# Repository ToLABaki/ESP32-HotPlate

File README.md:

# ESP32-HotPlate
A reflow soldering plate, using the ESP32 and the lvgl graphics library.

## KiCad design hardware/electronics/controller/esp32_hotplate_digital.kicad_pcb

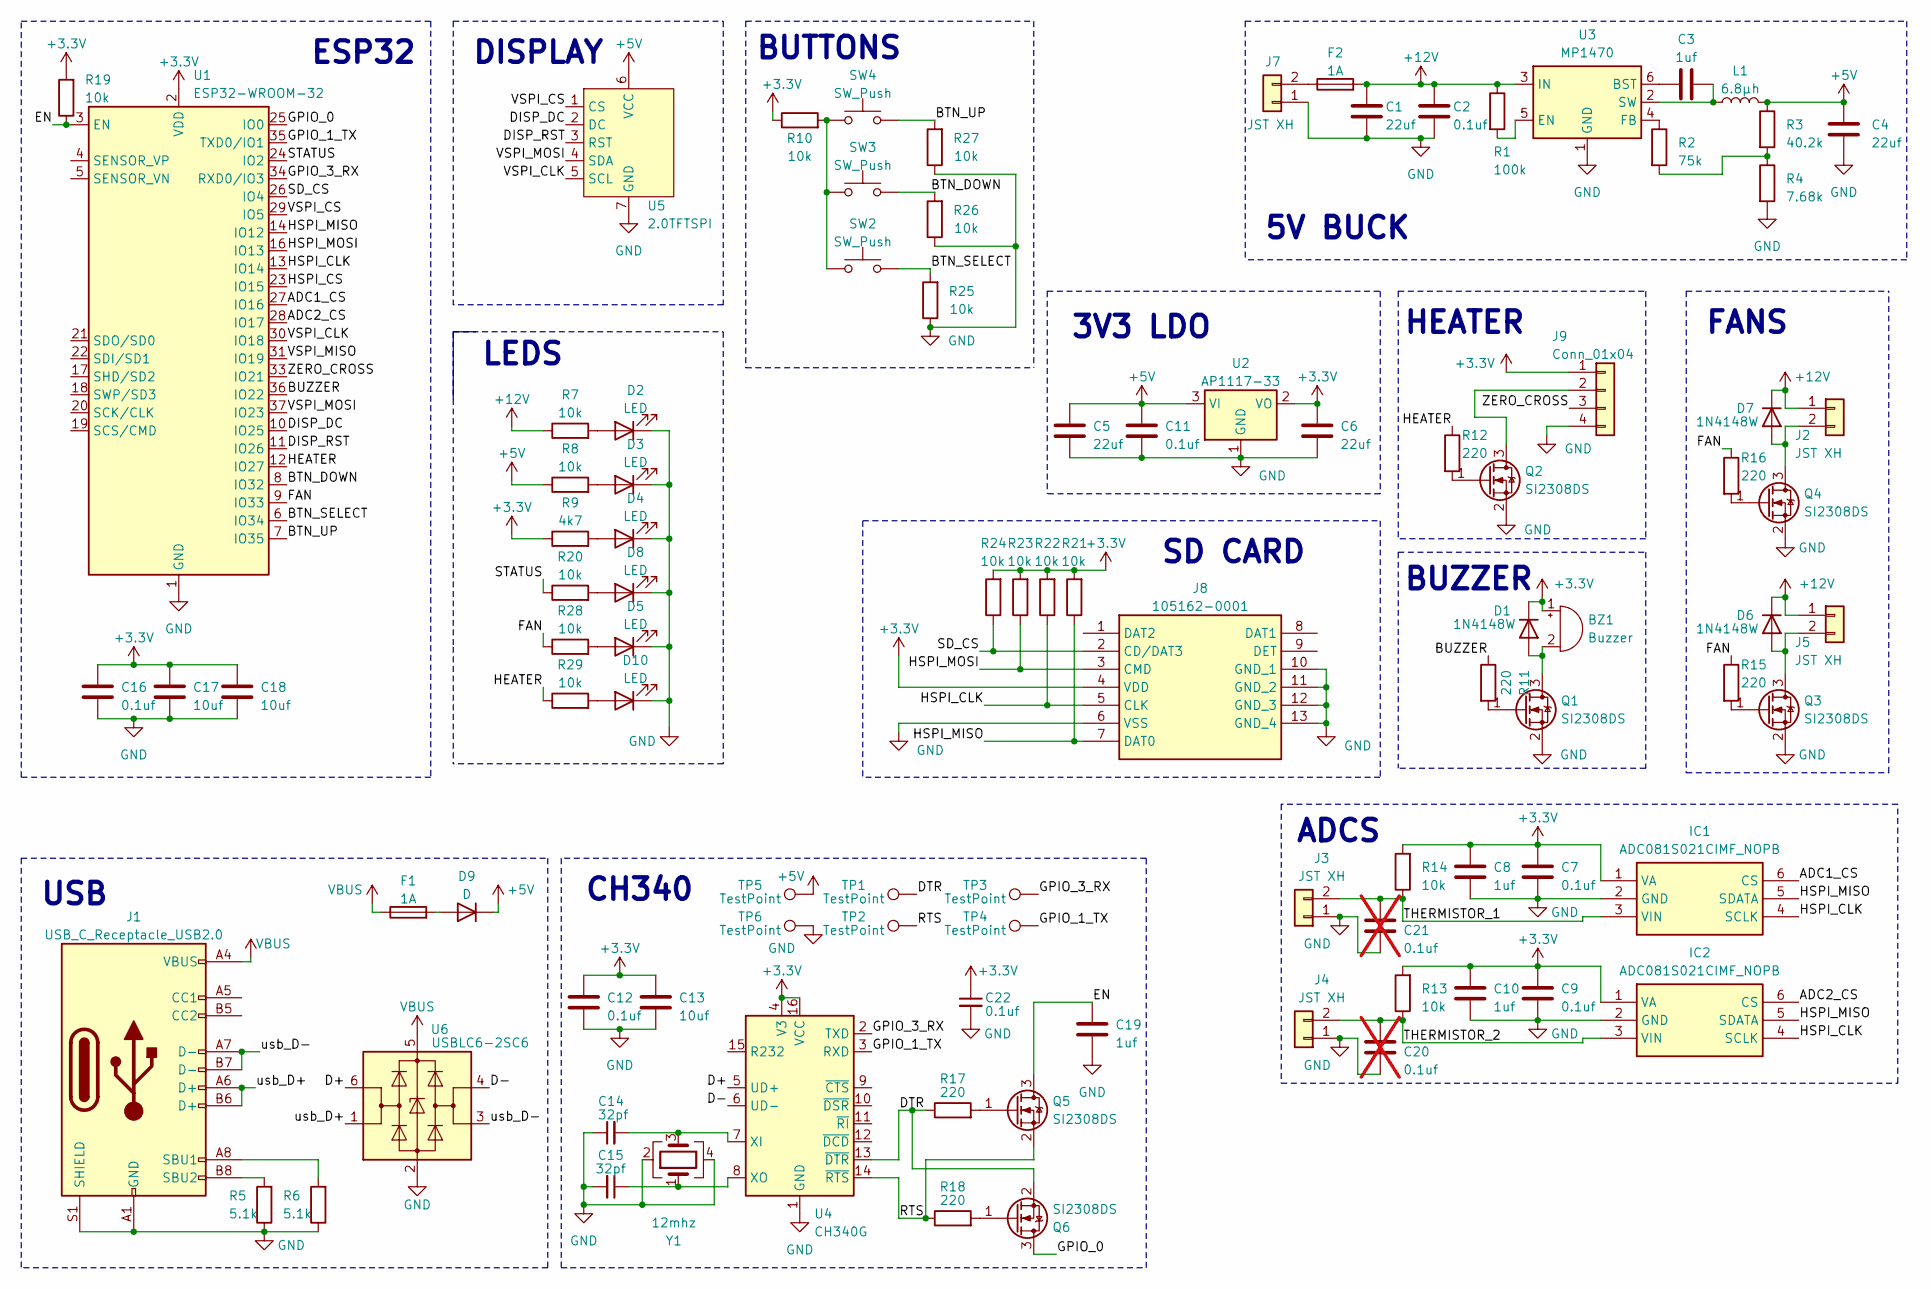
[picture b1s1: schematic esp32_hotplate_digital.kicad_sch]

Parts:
BZ1: Buzzer; PUIAudio_SMT_0825_S_4_R
C1, C4, C5, C6: 22uf; C_1206_3216Metric_Pad1.33x1.80mm_HandSolder
C2, C7, C9, C11, C12, C16: 0.1uf; C_0805_2012Metric_Pad1.18x1.45mm_HandSolder
C3, C8, C10, C19: 1uf; C_0805_2012Metric_Pad1.18x1.45mm_HandSolder
C13, C17, C18: 10uf; C_0805_2012Metric_Pad1.18x1.45mm_HandSolder
C14, C15: 32pf; C_0603_1608Metric_Pad1.08x0.95mm_HandSolder
C20, C21: 0.1uf; C_0805_2012Metric_Pad1.18x1.45mm_HandSolder; not fitted
C22: 0.1uf; C_0603_1608Metric_Pad1.08x0.95mm_HandSolder
D1, D6, D7: 1N4148W; D_SOD-128
D2, D3, D4, D5, D8, D10: LED; LED_0805_2012Metric_Pad1.15x1.40mm_HandSolder
D9: D; DIOM5226X240N
F1, F2: 1A; Fuse_1206_3216Metric
IC1, IC2: ADC081S021CIMF_NOPB; SOT95P280X145-6N; Mouser Part Number 926-AD081S021CIMFNPB
J1: USB_C_Receptacle_USB2.0; USB_C_Receptacle_HRO_TYPE-C-31-M-12
J2, J3, J4, J5, J7: JST XH; JST_XH_B2B-XH-A_1x02_P2.50mm_Vertical
J8: 105162-0001; TF-SMD_TF-PUSH; Mouser Part Number 538-105162-0001
J9: Conn_01x04; JST_XH_B4B-XH-A_1x04_P2.50mm_Vertical
L1: 6.8μh; L_Changjiang_FNR8040S
Q1, Q2, Q3, Q4, Q5, Q6: SI2308DS; SOT-23
R1: 100k; R_0805_2012Metric_Pad1.20x1.40mm_HandSolder
R2: 75k; R_0805_2012Metric_Pad1.20x1.40mm_HandSolder
R3: 40.2k; R_0805_2012Metric_Pad1.20x1.40mm_HandSolder
R4: 7.68k; R_0805_2012Metric_Pad1.20x1.40mm_HandSolder
R5, R6: 5.1k; R_0805_2012Metric_Pad1.20x1.40mm_HandSolder
R7, R8, R10, R13, R14, R19, R20, R21, R22, R23, R24, R25, R26, R27, R28, R29: 10k; R_0805_2012Metric_Pad1.20x1.40mm_HandSolder
R9: 4k7; R_0805_2012Metric_Pad1.20x1.40mm_HandSolder
R11, R12, R15, R16, R17, R18: 220; R_0805_2012Metric_Pad1.20x1.40mm_HandSolder
SW2, SW3, SW4: SW_Push; SW_SPST_TL3342
TP1, TP2, TP3, TP4, TP5, TP6: TestPoint; TestPoint_Pad_2.0x2.0mm
U1: ESP32-WROOM-32
U2: AP1117-33; SOT-223-3_TabPin2
U3: MP1470; TSOT-23-6
U4: CH340G; SOIC-16_3.9x9.9mm_P1.27mm
U5: 2.0TFTSPI; 2.0_TFT_SPI
U6: USBLC6-2SC6; SOT-23-6
Y1: 12mhz; Crystal_SMD_3225-4Pin_3.2x2.5mm

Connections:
+3.3V: BZ1.1 (-), C6.1, C7.1, C8.1, C9.1, C10.1, C12.1, C13.1, C16.1, C17.1, C18.1, C22.1, D1.1 (K), IC1.1 (VA), IC2.1 (VA), J8.4 (VDD), J9.1, R9.1, R10.1, R13.2, R14.2, R19.2, R21.2, R22.2, R23.2, R24.2, U1.2 (VDD), U2.2 (VO), U4.4 (V3), U4.16 (VCC)
+5V: C4.1, C5.1, C11.1, D9.1 (K), L1.2, R3.1, R8.1, TP5.1, U2.3 (VI), U5.6 (VCC)
+12V: C1.1, C2.1, D6.1 (K), D7.1 (K), F2.2, J2.1, J5.1, R1.1, R7.1, U3.3 (IN)
/ADC1_CS: IC1.6 (CS), U1.27 (IO16)
/ADC2_CS: IC2.6 (CS), U1.28 (IO17)
/BTN_DOWN: R26.2, SW3.2, U1.8 (IO32)
/BTN_SELECT: R25.2, SW2.2, U1.6 (IO34)
/BTN_UP: R27.2, SW4.2, U1.7 (IO35)
/BUZZER: R11.1, U1.36 (IO22)
/D+: U4.5 (UD+), U6.6 (I/O1)
/D-: U4.6 (UD-), U6.4 (I/O2)
/DISP_DC: U1.10 (IO25), U5.2 (DC)
/DISP_RST: U1.11 (IO26), U5.3 (RST)
/DTR: Q6.2 (S), R17.1, TP1.1, U4.13 (~DTR)
/EN: C19.2, Q5.3 (D), R19.1, U1.3 (EN)
/FAN: R15.1, R16.1, R28.1, U1.9 (IO33)
/GPIO_0: Q6.3 (D), U1.25 (IO0)
/GPIO_1_TX: TP4.1, U1.35 (TXD0/IO1), U4.3 (RXD)
/GPIO_3_RX: TP3.1, U1.34 (RXD0/IO3), U4.2 (TXD)
/HEATER: R12.1, R29.1, U1.12 (IO27)
/HSPI_CLK: IC1.4 (SCLK), IC2.4 (SCLK), J8.5 (CLK), R22.1, U1.13 (IO14)
/HSPI_CS: U1.23 (IO15)
/HSPI_MISO: IC1.5 (SDATA), IC2.5 (SDATA), J8.7 (DAT0), R21.1, U1.14 (IO12)
/HSPI_MOSI: J8.3 (CMD), R23.1, U1.16 (IO13)
/RTS: Q5.2 (S), R18.1, TP2.1, U4.14 (~RTS)
/SD_CS: J8.2 (CD/DAT3), R24.1, U1.26 (IO4)
/STATUS: R20.1, U1.24 (IO2)
/THERMISTOR_1: C21.1, IC1.3 (VIN), J3.2, R14.1
/THERMISTOR_2: C20.1, IC2.3 (VIN), J4.2, R13.1
/VSPI_CLK: U1.30 (IO18), U5.5 (SCL)
/VSPI_CS: U1.29 (IO5), U5.1 (CS)
/VSPI_MISO: U1.31 (IO19)
/VSPI_MOSI: U1.37 (IO23), U5.4 (SDA)
/ZERO_CROSS: J9.3, U1.33 (IO21)
/usb_D+: J1.A6 (D+), J1.B6 (D+), U6.1 (I/O1)
/usb_D-: J1.A7 (D-), J1.B7 (D-), U6.3 (I/O2)
GND: C1.2, C2.2, C4.2, C5.2, C6.2, C7.2, C8.2, C9.2, C10.2, C11.2, C12.2, C13.2, C14.1, C15.2, C16.2, C17.2, C18.2, C19.1, C20.2, C21.2, C22.2, D2.1 (K), D3.1 (K), D4.1 (K), D5.1 (K), D8.1 (K), D10.1 (K), IC1.2 (GND), IC2.2 (GND), J1.A1 (GND), J1.A12 (GND), J1.B1 (GND), J1.B12 (GND), J1.S1 (SHIELD), J3.1, J4.1, J7.1, J8.6 (VSS), J8.10 (GND_1), J8.11 (GND_2), J8.12 (GND_3), J8.13 (GND_4), J9.4, Q1.2 (S), Q2.2 (S), Q3.2 (S), Q4.2 (S), R4.2, R5.1, R6.1, R25.1, R26.1, R27.1, TP6.1, U1.1 (GND), U1.15 (GND), U1.38 (GND), U1.39 (GND), U2.1 (GND), U3.1 (GND), U4.1 (GND), U5.7 (GND), U6.2 (GND), Y1.2, Y1.4
unnamed: BZ1.2 (+), D1.2 (A), Q1.3 (D)
unnamed: D2.2 (A), R7.2
unnamed: D3.2 (A), R8.2
unnamed: D4.2 (A), R9.2
unnamed: D5.2 (A), R28.2
unnamed: D6.2 (A), J5.2, Q3.3 (D)
unnamed: D7.2 (A), J2.2, Q4.3 (D)
unnamed: D8.2 (A), R20.2
unnamed: D9.2 (A), F1.2
unnamed: D10.2 (A), R29.2
unnamed: J1.A8 (SBU1), R6.2
unnamed: J1.B8 (SBU2), R5.2
unnamed: F2.1, J7.2
unnamed: J9.2, Q2.3 (D)
unnamed: Q1.1 (G), R11.2
unnamed: Q2.1 (G), R12.2
unnamed: Q3.1 (G), R15.2
unnamed: Q4.1 (G), R16.2
unnamed: Q5.1 (G), R17.2
unnamed: Q6.1 (G), R18.2
unnamed: R2.2, R3.2, R4.1
unnamed: R10.2, SW2.1, SW3.1, SW4.1
unnamed: C3.1, U3.6 (BST)
unnamed: R1.2, U3.5 (EN)
unnamed: R2.1, U3.4 (FB)
unnamed: C3.2, L1.1, U3.2 (SW)
unnamed: C14.2, U4.7 (XI), Y1.3
unnamed: C15.1, U4.8 (XO), Y1.1
VBUS: F1.1, J1.A4 (VBUS), J1.A9 (VBUS), J1.B4 (VBUS), J1.B9 (VBUS), U6.5 (VBUS)

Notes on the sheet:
ESP32
HEATER
5V BUCK
FANS
BUTTONS
BUZZER
CH340
SD CARD
DISPLAY
ADCS
LEDS
3V3 LDO
USB

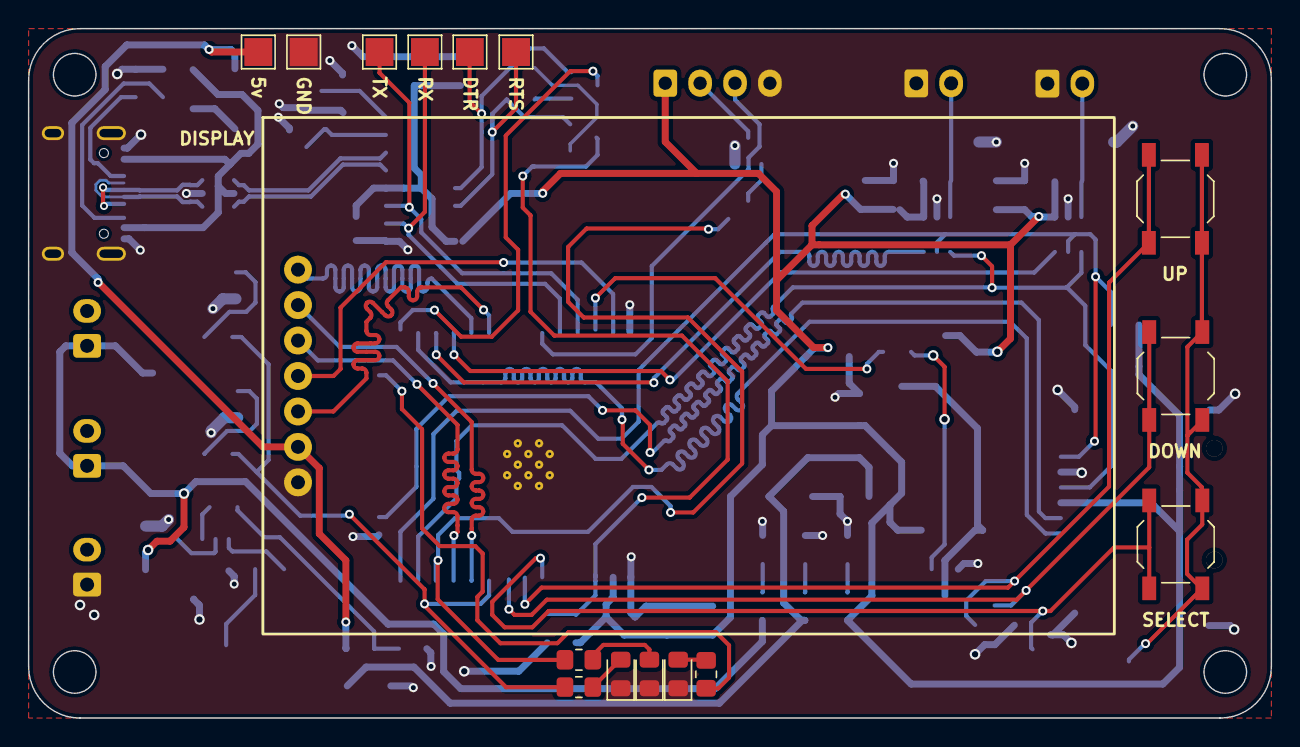
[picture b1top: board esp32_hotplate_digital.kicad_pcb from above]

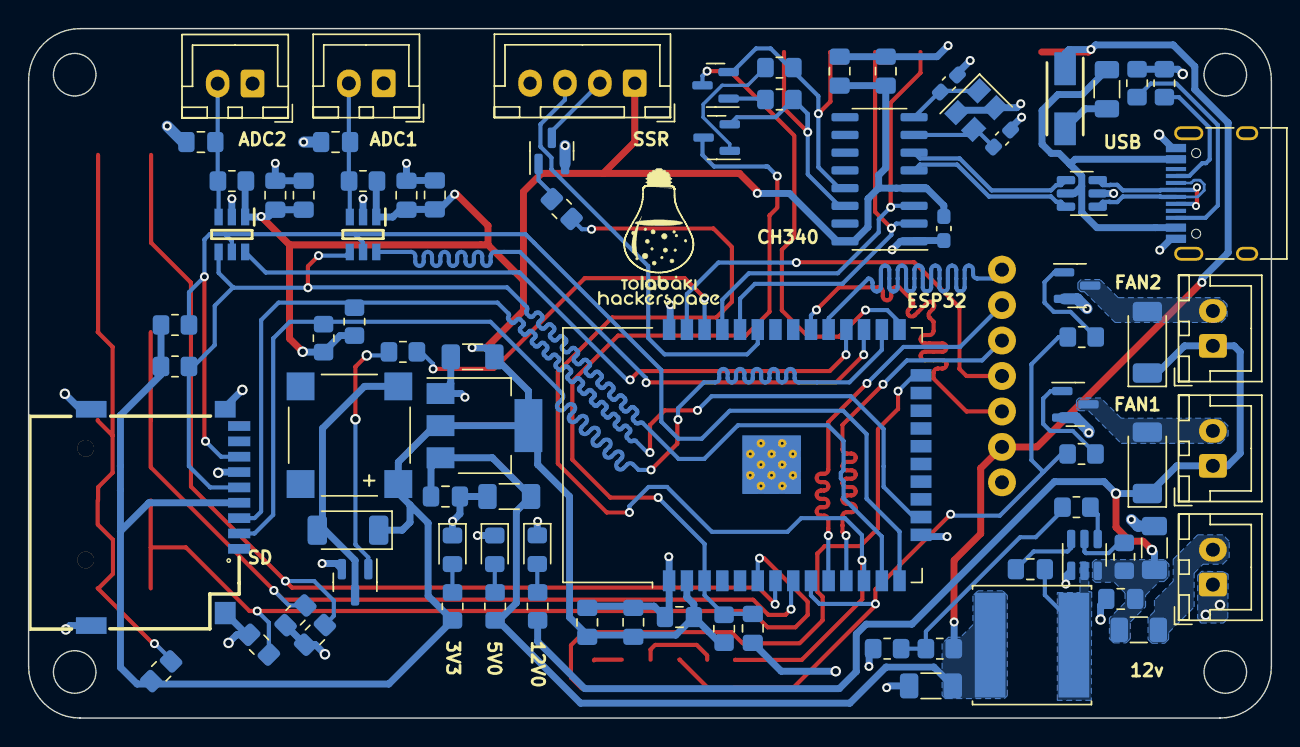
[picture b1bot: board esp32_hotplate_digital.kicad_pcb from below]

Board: 2 copper layers, 89.1 x 49.4 mm, 97 parts (81 on the bottom side), 64 nets.

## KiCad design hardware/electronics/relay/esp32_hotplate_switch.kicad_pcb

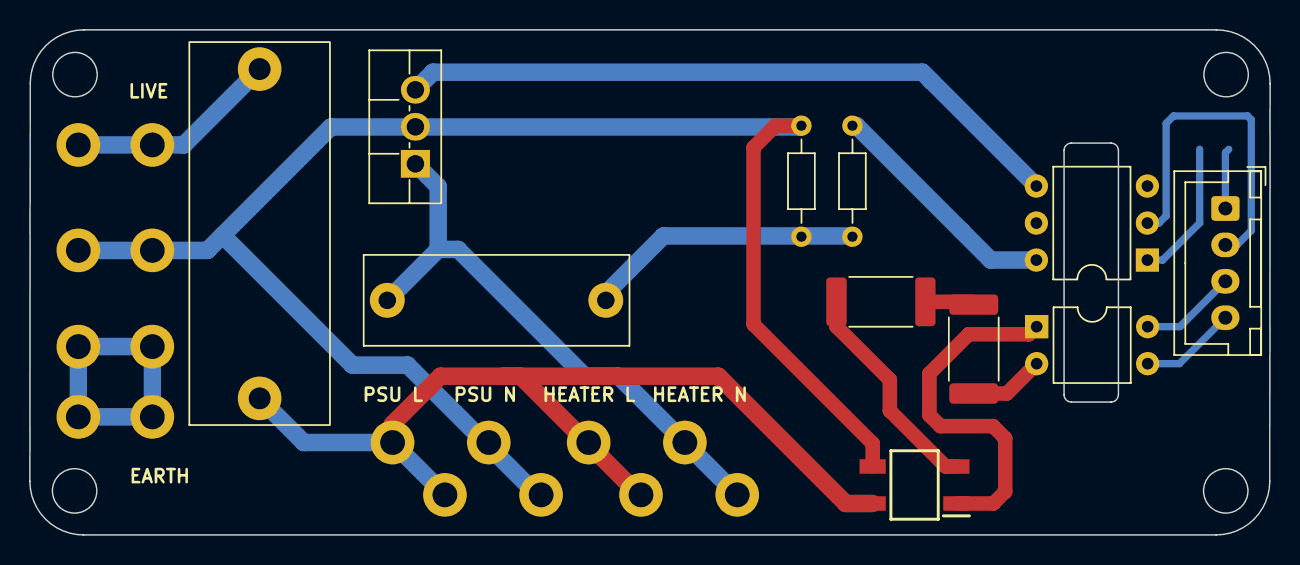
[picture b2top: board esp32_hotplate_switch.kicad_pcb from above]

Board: 2 copper layers, 85.1 x 34.7 mm, 20 parts (1 on the bottom side), 17 nets.

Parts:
C1: 0.1uf/275v; C_Rect_L18.0mm_W6.0mm_P15.00mm_FKS3_FKP3
D5: S380; SOP254P650X170-4N
F1: Fuse; ZHL78
J1, J2, J3, J4, J5, J6, J8, J9: Conn_01x01; QK_DISCONNECT
J7: Conn_01x04; JST_XH_B4B-XH-A_1x04_P2.50mm_Vertical
Q1: BTA24-600BWRG; TO-220F-3_Vertical
R1: 470r; R_Axial_DIN0204_L3.6mm_D1.6mm_P7.62mm_Horizontal
R2: 360r; R_Axial_DIN0204_L3.6mm_D1.6mm_P7.62mm_Horizontal
R4: 220r; R_0805_2012Metric_Pad1.20x1.40mm_HandSolder
R5, R6: 22k; R_2512_6332Metric_Pad1.40x3.35mm_HandSolder
U1: MOC3022M; DIP-6_W7.62mm
U2: LTV-817; DIP-4_W7.62mm

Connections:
Earth: J3.1, J9.1
GND: J7.4, U2.3
LINE: D5.4 (~_2), F1.1, J5.1, J6.1
NEUT: D5.3 (~_1), J2.1, J8.1, Q1.2 (MT2), R1.1
unnamed: C1.1, R1.2, R2.1
unnamed: D5.1 (+), U2.1
unnamed: D5.2 (-), R6.1
unnamed: F1.2, J1.1
unnamed: C1.2, J4.1, Q1.1 (MT1)
unnamed: J7.1, R4.2
unnamed: J7.2, U1.2
unnamed: J7.3, U2.4
unnamed: Q1.3 (G), U1.4
unnamed: R2.2, U1.6
unnamed: R4.1, U1.1
unnamed: R5.1, R6.2
unnamed: R5.2, U2.2

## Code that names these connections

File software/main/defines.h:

#ifndef DEFINES_H
#define DEFINES_H


#include <stdbool.h>
#include <stdio.h>
#include <stdlib.h>
#include <string.h>
#include <wchar.h>      /* wint_t */

#include <sys/unistd.h>
#include <sys/stat.h>

#include "freertos/FreeRTOS.h"
#include "freertos/task.h"
#include "esp_freertos_hooks.h"
#include "freertos/semphr.h"
#include "freertos/timers.h"
#include "esp_system.h"
#include "driver/gpio.h"
#include "esp_err.h"
#include "esp_log.h"
#include "esp_spiffs.h"
#include "esp_timer.h"
#include "esp_vfs_fat.h"
#include "sdmmc_cmd.h"
#include "jsmn.h"




/* Littlevgl specific */
#ifdef LV_LVGL_H_INCLUDE_SIMPLE
#include "lvgl.h"
#else
#include "lvgl/lvgl.h"
#endif
#include "lvgl_helpers.h"



#define GUI_SEMAPHORE_WAIT while(xSemaphoreTake(xGuiSemaphore, portMAX_DELAY) == pdFALSE){taskYIELD();}
#define LV_TICK_PERIOD_MS 1

#define STATUS_PIN      GPIO_NUM_2
#define HEATER_PIN      GPIO_NUM_27
#define FAN_PIN         GPIO_NUM_33

#define BUZZER_PIN      GPIO_NUM_22
#define UP_PIN          GPIO_NUM_35
#define DOWN_PIN        GPIO_NUM_32
#define SELECT_PIN      GPIO_NUM_34

#define HSPI_MISO   GPIO_NUM_12
#define HSPI_CLK    GPIO_NUM_14
#define HSPI_MOSI    GPIO_NUM_13

#define ADC_SAMPLES_AVG_ARRAY_SIZE 20



enum states{main_menu, reflow_menu, select_menu, error_menu, heat_menu} state;



SemaphoreHandle_t xGuiSemaphore;

extern lv_indev_t * my_indev ;



extern volatile uint32_t MENUCHANGED_DISABLEBUTTONS;


enum reflow_states{preheat = 0, soak = 1, reflow_ramp = 2, reflow = 3, cooldown  = 4 };
extern enum reflow_states reflow_state;
struct reflow_phase{
    uint16_t start_temp;
    uint16_t finish_temp;
    uint32_t time;
};
struct reflow_profile{
    struct reflow_phase phase[5];
    
  
    char label[60];
};

extern struct reflow_profile * profiles;

extern uint32_t profile_selected;

extern uint32_t profiles_num;

extern volatile float internal_temp;
extern volatile float external_temp;


struct selection{
    char label[20];
    uint32_t value;

    lv_obj_t * associated_button;
    struct selection_items *items_array;
    uint32_t items_array_length;
    uint32_t selected_index;
};

struct selection_items{
    char label[45];
    uint32_t value;
    void * data;

    lv_obj_t *associated_button;
    struct selection *associated_selection;

};

struct reflow_params{
    uint32_t function;
    uint32_t sensor;
    spi_device_handle_t sensor_handle;
    
    uint32_t fans;
    //function == 0 REFLOW
    uint32_t heat;
    //function == 1 HEATING
    struct reflow_profile *profile;
};

extern volatile struct reflow_params *reflow_selected_params;

#define CONFIG_LIST_SIZE 6
extern struct selection *config_list;

extern esp_err_t init_data();
extern esp_err_t init_sdcard_data();
extern esp_err_t init_data_generic();


extern float current_temp;
extern float target_temp;
extern uint32_t total_time_ms;
extern uint32_t elapsed_time_ms;






#endif

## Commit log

2023-07-26 adding digital board
2023-07-26 adding esp32 firmware
2023-07-26 adding switch board + updating README
2023-07-26 updating code README + tweaks in adc081s.c
2023-08-02 attempting to get the sd card working with SPI
2023-08-02 spi sd card working
2023-08-10 fixes for revision2
2023-08-13 controller can now draw reflow profiles from the sd card, if no card is available a default profile will be loaded
2023-08-15 added warning screen for no sd + fixed init semaphore error
2023-08-15 fixed main menu not showing the correct reflow profile label
2023-08-22 finalized the controller version 2
2023-08-22 redraw polygons with 45* angles
2023-09-14 updated code + added 3d pintable parts + added thermal isolation pcb
